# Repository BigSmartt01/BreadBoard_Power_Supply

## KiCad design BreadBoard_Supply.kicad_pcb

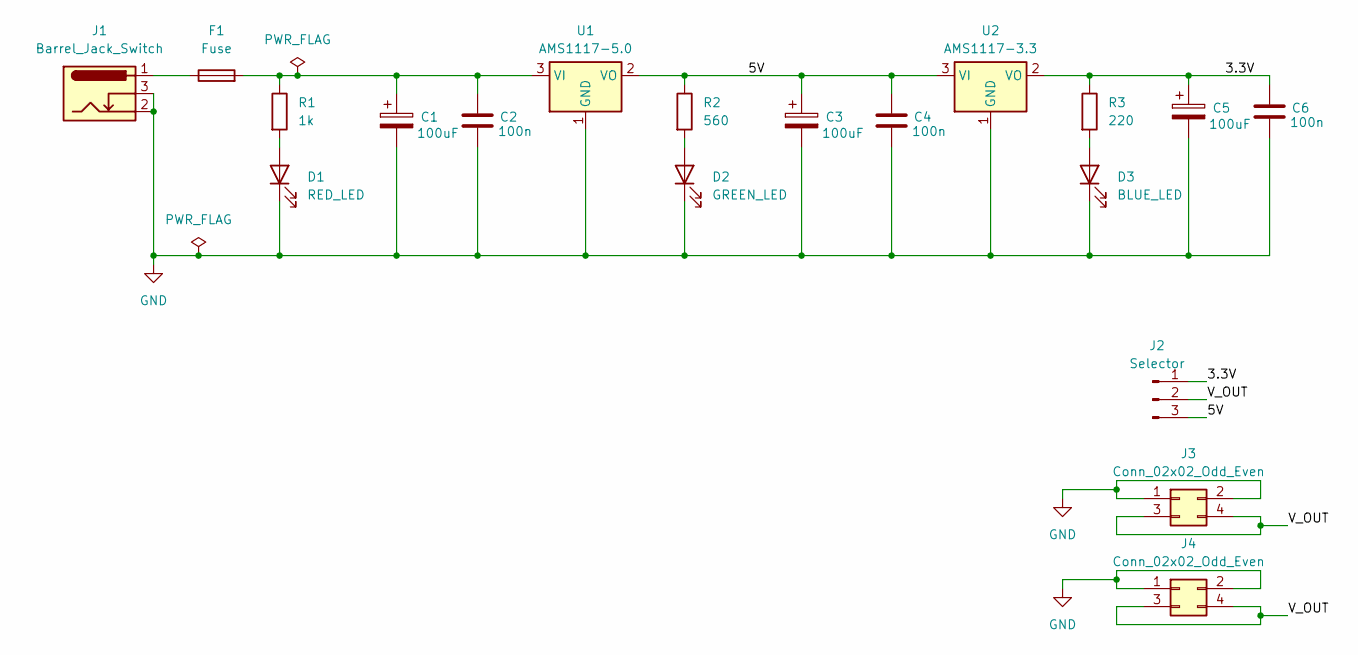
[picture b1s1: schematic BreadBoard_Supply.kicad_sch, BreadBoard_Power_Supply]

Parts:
C1, C3, C5: 100uF; CP_Elec_5x5.8
C2, C4, C6: 100n; C_1206_3216Metric_Pad1.33x1.80mm_HandSolder
D1: RED_LED; LED_1206_3216Metric_Pad1.42x1.75mm_HandSolder
D2: GREEN_LED; LED_1206_3216Metric_Pad1.42x1.75mm_HandSolder
D3: BLUE_LED; LED_1206_3216Metric_Pad1.42x1.75mm_HandSolder
F1: Fuse; Fuse_1206_3216Metric_Pad1.42x1.75mm_HandSolder
J1: Barrel_Jack_Switch; BarrelJack_Horizontal
J2: Selector; PinHeader_1x03_P2.54mm_Vertical
J3, J4: Conn_02x02_Odd_Even; PinHeader_2x02_P2.54mm_Vertical
R1: 1k; R_1206_3216Metric_Pad1.42x1.75mm_HandSolder
R2: 560; R_1206_3216Metric_Pad1.42x1.75mm_HandSolder
R3: 220; R_1206_3216Metric_Pad1.42x1.75mm_HandSolder
U1: AMS1117-5.0; SOT-223-3_TabPin2
U2: AMS1117-3.3; SOT-223-3_TabPin2

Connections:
/3.3V: C5.1, C6.1, J2.1, R3.1, U2.2 (VO)
/5V: C3.1, C4.1, J2.3, R2.1, U1.2 (VO), U2.3 (VI)
/V_OUT: J2.2, J3.3, J3.4, J4.3, J4.4
GND: C1.2, C2.2, C3.2, C4.2, C5.2, C6.2, D1.1 (K), D2.1 (K), D3.1 (K), J1.2, J1.3, J3.1, J3.2, J4.1, J4.2, U1.1 (GND), U2.1 (GND)
unnamed: D1.2 (A), R1.2
unnamed: D2.2 (A), R2.2
unnamed: D3.2 (A), R3.2
unnamed: F1.1, J1.1
unnamed: C1.1, C2.1, F1.2, R1.1, U1.3 (VI)

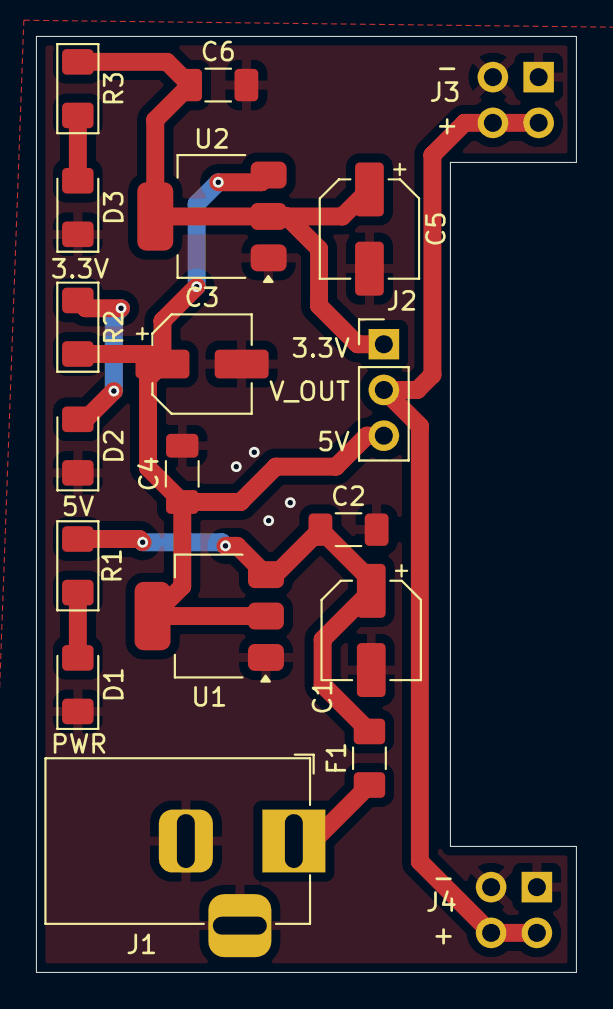
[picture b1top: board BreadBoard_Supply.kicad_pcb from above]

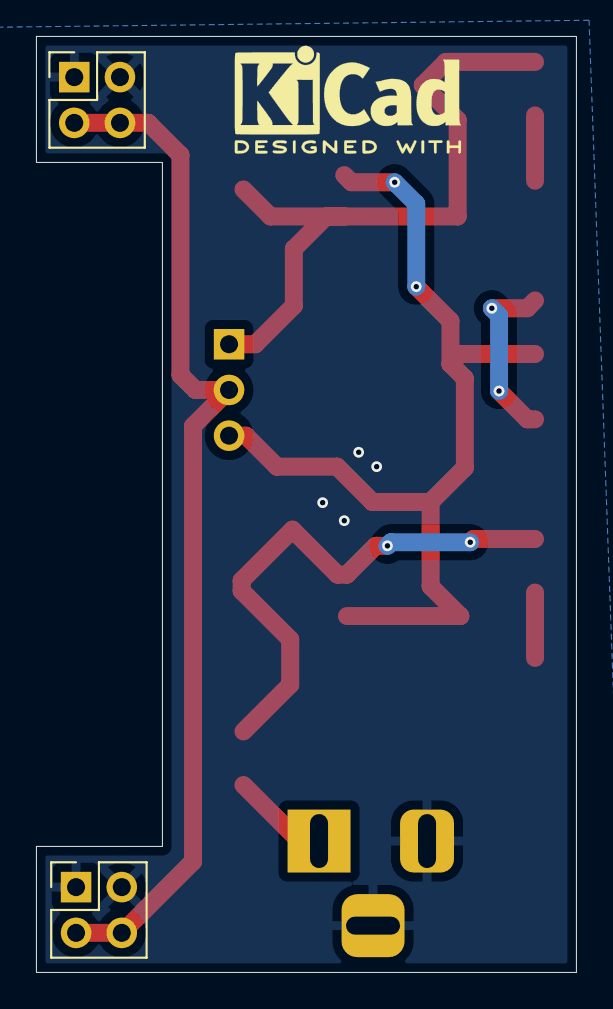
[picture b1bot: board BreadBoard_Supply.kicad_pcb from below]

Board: 2 copper layers, 30.0 x 52.0 mm, 19 parts (2 on the bottom side), 9 nets.

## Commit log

2026-01-27 Initial Push
2026-01-28 Completed with DC input
